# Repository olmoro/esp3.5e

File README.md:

# esp3.5e
 Модуль управления зарядным устройством

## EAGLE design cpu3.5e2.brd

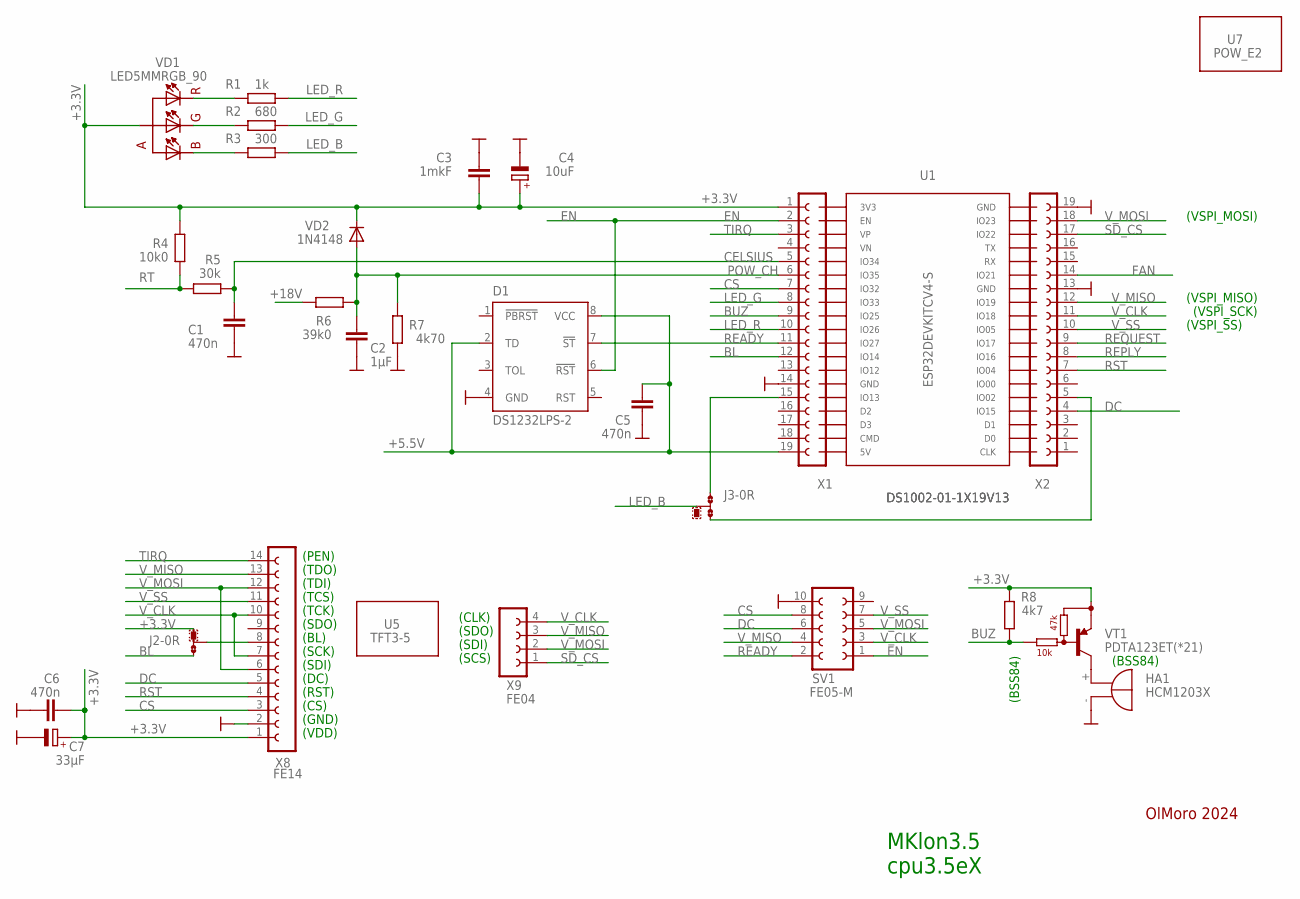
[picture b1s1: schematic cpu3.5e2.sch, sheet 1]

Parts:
C1, C5, C6: 470n; C0805
C2: 1µF; C0805
C3: 1mkF; C0805
C4: 10uF; CT3528
C7: 33µF; CT6032
D1: DS1232LPS-2; SO-08
HA1: HCM1203X; BMT1205XH7.5
J2, J3: 0R-JUMPB; B0R-JMP
R1: 1k; R0805
R2: 680; R0805
R3: 300; R0805
R4: 10k0; R0805
R5: 30k; R0805
R6: 39k0; R0805
R7: 4k70; R0805
R8: 4k7; R0805
SV1: FE05-M; FE05-2M
U1: ESP32DEVKITCV4-S
U5: TFT3-5
U7: POW_E2; POW3_5
VD1: LED5MMRGB_90
VD2: 1N4148; MINIMELF
VT1: PDTA123ET(*21); SOT23-BEC
X1, X2: DS1002-01-1X19V13
X8: FE14
X9: FE04

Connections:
+3.3V: C3.1, C4.+, C6.1, C7.+, J2.1, R4.1, R8.2, VD1.P$3 (A), VD2.C, VT1.E, X1.1, X8.1
+5.5V: C5.1, D1.2 (TD), D1.8 (VCC), X1.19; also elsewhere on the board
+18V: R6.2; also elsewhere on the board
BL: J2.3, X1.12
BUZ: R8.1, VT1.B, X1.9
CELSIUS: C1.1, R5.2, X1.5
CS: SV1.8, X1.7, X8.3
DC: SV1.6, X2.4, X8.5
EN: D1.6 (!RST), SV1.1, X1.2; also elsewhere on the board
FAN: X2.14; also elsewhere on the board
GND: C1.2, C2.2, C3.2, C4.-, C5.2, C6.2, C7.-, D1.4 (GND), HA1.-, R7.1, SV1.10, X1.14, X2.13, X2.19, X8.2; also elsewhere on the board
LED_B: J3.2, J3.3, R3.1, X1.15
LED_G: R2.1, X1.8
LED_R: R1.1, X1.10
unnamed: J2.2, X8.8
unnamed: J3.1, X2.5
unnamed: HA1.+, VT1.C
unnamed: R2.2, VD1.P$2 (GREEN)
unnamed: R1.2, VD1.P$4 (RED)
unnamed: R3.2, VD1.P$1 (BLUE)
POW_CH: C2.1, R6.1, R7.2, VD2.A, X1.6
READY: D1.7 (!ST), SV1.2, X1.11; also elsewhere on the board
REPLY: X2.8; also elsewhere on the board
REQUEST: X2.9; also elsewhere on the board
RST: X2.7, X8.4
RT: R4.2, R5.1; also elsewhere on the board
SD_CS: X2.17, X9.1
TIRQ: X1.3, X8.14
V_CLK: SV1.3, X2.11, X8.7, X8.10, X9.4
V_MISO: SV1.4, X2.12, X8.13, X9.3
V_MOSI: SV1.5, X2.18, X8.6, X8.12, X9.2
V_SS: SV1.7, X2.10, X8.11

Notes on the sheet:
(VSPI_MOSI)
(VSPI_MISO)
(VSPI_SCK)
(VSPI_SS)
MKlon3.5 cpu3.5eX
OlMoro 2024
(CS)
(RST)
(DC)
(SDI)
(SCK)
(VDD)
(GND)
(BL)
(SDO)
(TCK)
(TCS)
(TDI)
(TDO)
(PEN)
(CLK)
(SCS)
(BSS84)

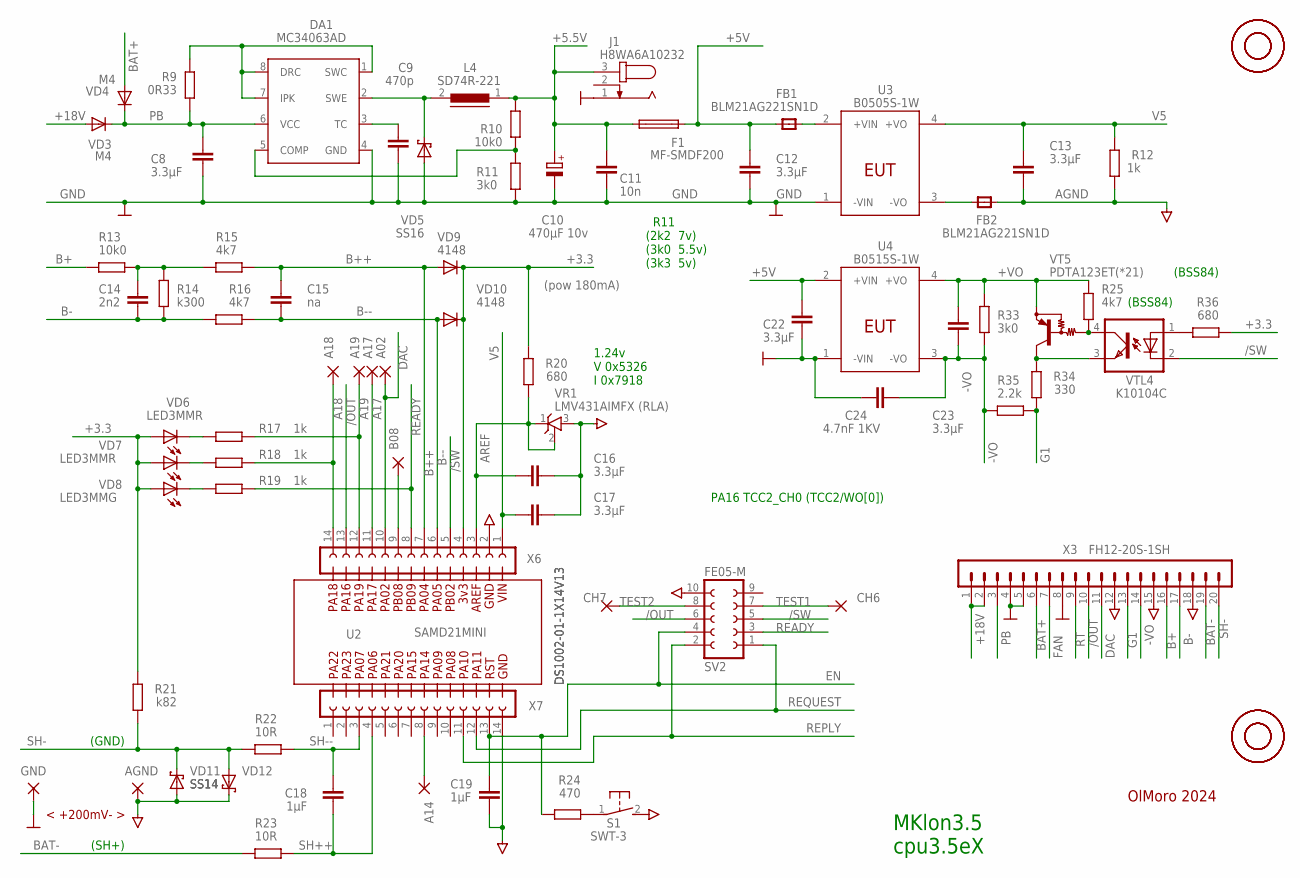
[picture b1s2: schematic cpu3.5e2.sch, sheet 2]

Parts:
A02, A17, A18, A19: 1,6/0,8
A14: WIREPAD1,6/0,8; 1,6/0,8
AGND: AGND; 4,16O1,6
B08: WIREPAD1,6/0,8; 1,6/0,8
C8, C12, C13, C16, C17, C22, C23: 3.3µF; C0805
C9: 470p; C0805
C10: 470µF 10v; E5-8,5
C11: 10n; C0805
C14: 2n2; C0805
C15: na; C0805
C18, C19: 1µF; C0805
C24: 4.7nF 1KV; C050-024X044
CH6, CH7: 1,6/0,8
DA1: MC34063AD; SO08
F1: MF-SMDF200; MF-SMDF050
FB1, FB2: BLM21AG221SN1D; 0805
GND: GND; 4,16O1,6
J1: H8WA6A10232; SPC4077
L4: SD74R-221; DR74
R9: 0R33; R0805
R10, R13: 10k0; R0805
R11, R33: 3k0; R0805
R12, R17, R18, R19: 1k; R0805
R14: k300; R0805
R15, R16, R25: 4k7; R0805
R20, R36: 680; R0805
R21: k82; R0805
R22, R23: 10R; R0805
R24: 470; R0805
R34: 330; R0805
R35: 2.2k; R0805
S1: SWT-3; B3F-31XX
SV2: FE05-M; FE05-2M
U2: SAMD21MINI
U3: B0505S-1W; HLK-1D1212
U4: B0515S-1W; HLK-1D1212
U$6, U$15, U$16, U$18: M3X20
U$19, U$21, U$23, U$27: M3X12
VD3, VD4: M4; DO214AC
VD5: SS16; DO214AC
VD6, VD7: LED3MMR
VD8: LED3MMG
VD9, VD10: 4148; MINIMELF
VD11, VD12: SS14; DO214AC
VR1: LMV431AIMFX (RLA); SOT23
VT5: PDTA123ET(*21); SC59-BEC
VTL4: K10104C; SMD4-7
X3: FH12-20S-1SH
X6, X7: DS1002-01-1X14V13

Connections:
+3.3: R20.1, R21.2, R36.1, VD6.A, VD7.A, VD8.A, VD9.C, VD10.C, X6.4
+5.5V: C10.+, C11.1, F1.1, J1.3, L4.1, R10.2; also elsewhere on the board
+5V: C12.1, C22.2, F1.2, FB1.1, U4.2 (+VIN)
+18V: VD3.A, X3.1, X3.2; also elsewhere on the board
+VO: C23.2, R25.2, R33.2, U4.4 (+VO), VT5.E
-VO: C23.1, C24.2, R33.1, R35.2, U4.3 (-VO), X3.14
/OUT: SV2.6, X3.10, X6.13
/SW: SV2.5, VTL4.2 (C), X6.5
A17: A17.1, X6.11
A18: A18.1, R18.2, X6.14
A19: A19.1, R17.2, X6.12
AGND: AGND.1, C13.2, C16.2, C17.2, C19.2, FB2.2, R12.1, S1.2 (S), SV2.10, VD11.A, VD12.C, VR1.3 (A), X3.12, X3.15, X3.18, X6.2, X7.14
AREF: C16.1, R20.2, VR1.1 (C), VR1.2 (R), X6.3
B+: R13.2, X3.16
B++: C15.1, R15.2, VD9.A, X6.7
B-: C14.2, R14.2, R16.1, X3.17
B--: C15.2, R16.2, VD10.A, X6.6
BAT+: VD4.A, X3.6
BAT-: R23.2, X3.19
DAC: A02.1, X3.11, X6.10
EN: C19.1, R24.1, SV2.4, X7.13; also elsewhere on the board
FAN: X3.7; also elsewhere on the board
G1: R34.1, R35.1, X3.13
GND: C8.2, C9.2, C10.-, C11.2, C12.2, C22.1, C24.1, DA1.4 (GND), GND.1, J1.1, R11.1, U3.1 (-VIN), U4.1 (-VIN), VD5.A, X3.4, X3.5, X3.8; also elsewhere on the board
unnamed: A14.1, X7.8
unnamed: B08.1, X6.9
unnamed: R18.1, VD7.K (C)
unnamed: R17.1, VD6.K (C)
unnamed: R19.1, VD8.K (C)
unnamed: R34.2, VT5.C, VTL4.3 (EMIT)
unnamed: R25.1, VT5.B, VTL4.4 (COL)
unnamed: DA1.1 (SWC), DA1.7 (IPK), DA1.8 (DRC), R9.2
unnamed: DA1.2 (SWE), L4.2, VD5.C
unnamed: R24.2, S1.1
unnamed: C9.1, DA1.3 (TC)
unnamed: DA1.5 (COMP), R10.1, R11.2
unnamed: R36.2, VTL4.1 (A)
unnamed: C14.1, R13.1, R14.1, R15.1
unnamed: FB1.2, U3.2 (+VIN)
unnamed: FB2.1, U3.3 (-VO)
PB: C8.1, DA1.6 (VCC), R9.1, VD3.C, VD4.C, X3.3
READY: R19.2, SV2.3, X6.8; also elsewhere on the board
REPLY: SV2.2, X7.11; also elsewhere on the board
REQUEST: SV2.1, X7.12; also elsewhere on the board
RT: X3.9; also elsewhere on the board
SH++: C18.1, R23.1, X7.4
SH-: R21.1, R22.2, VD11.C, VD12.A, X3.20
SH--: C18.2, R22.1, X7.3
TEST1: CH6.1, SV2.7
TEST2: CH7.1, SV2.8
V5: C13.1, C17.1, R12.2, U3.4 (+VO), X6.1

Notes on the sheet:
MKlon3.5 cpu3.5eX
PA16 TCC2_CH0 (TCC2/WO[0])
(pow 180mA)
OlMoro 2024
R11 (2k2 7v) (3k0 5.5v) (3k3 5v)
(SH+)
(GND)
1.24v V 0x5326 I 0x7918
< +200mV- >
(BSS84)

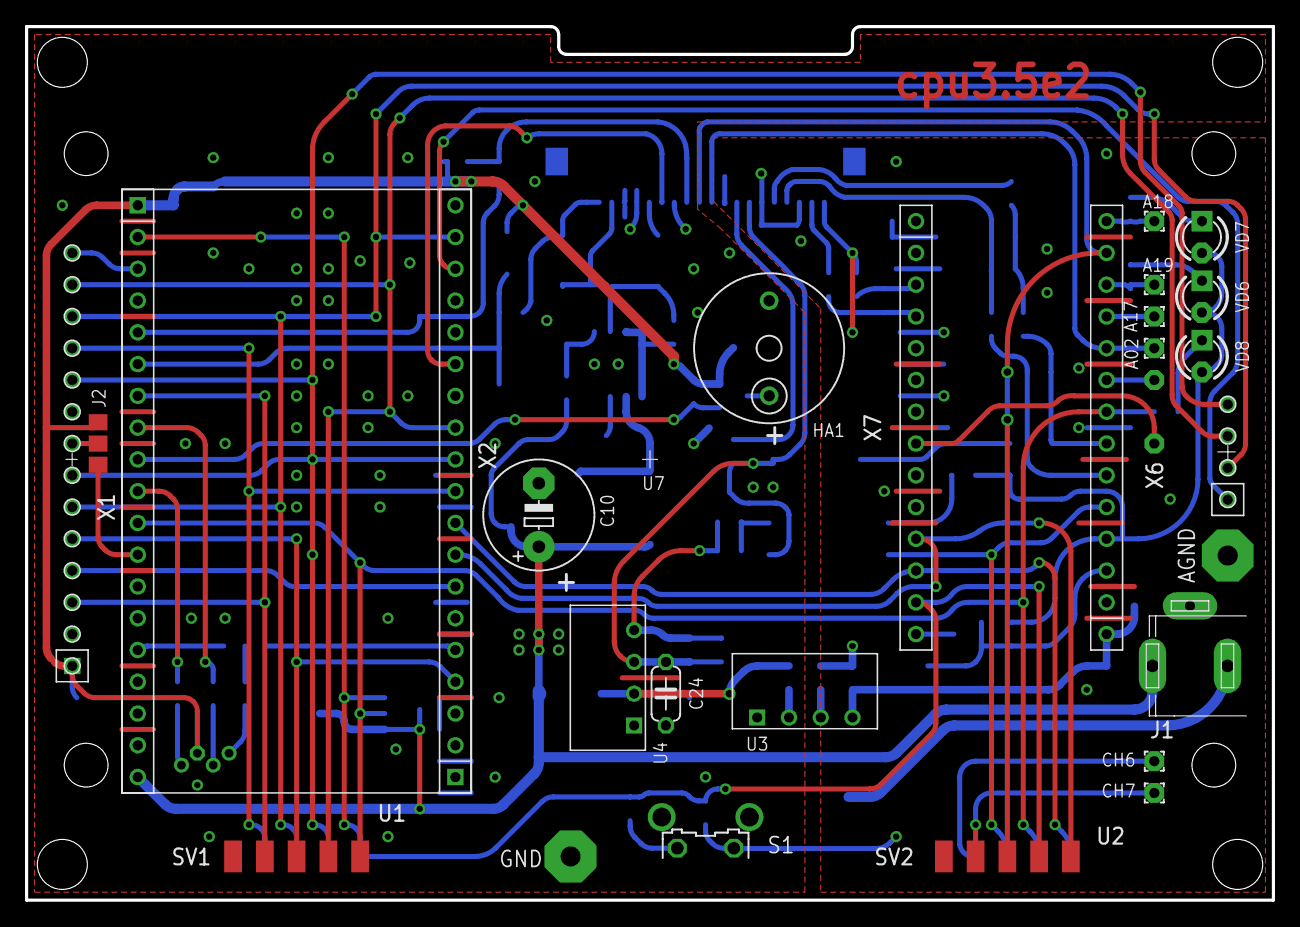
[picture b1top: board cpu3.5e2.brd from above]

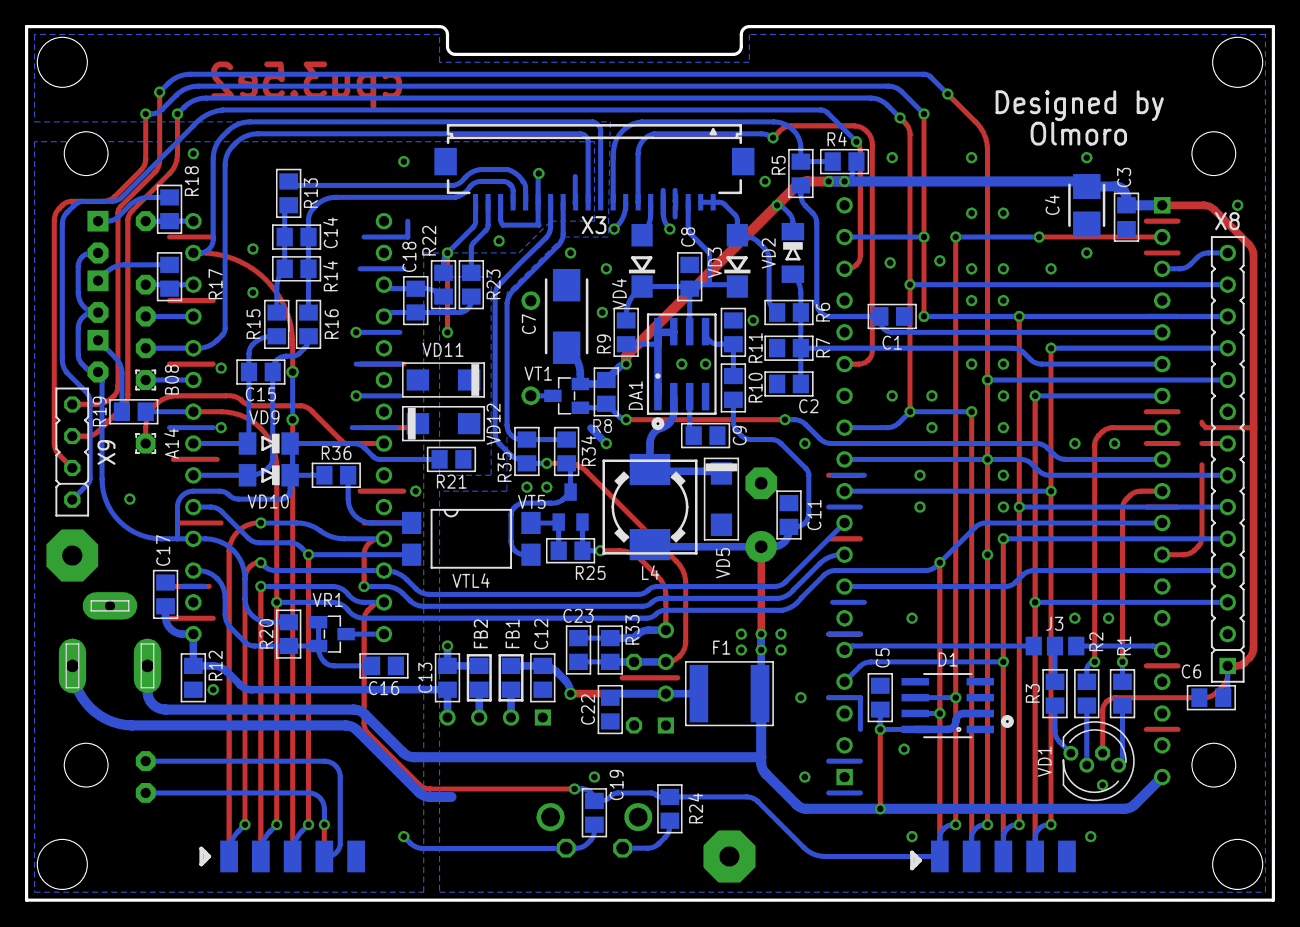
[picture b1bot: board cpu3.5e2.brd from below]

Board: 2 copper layers, 99.7 x 69.8 mm, 111 parts (78 on the bottom side), 74 nets.

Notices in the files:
parts and their libraries:
microbuilder_v2: This work is placed in the public domain, and may be freely used for commercial and non-commercial work with the following conditions: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
